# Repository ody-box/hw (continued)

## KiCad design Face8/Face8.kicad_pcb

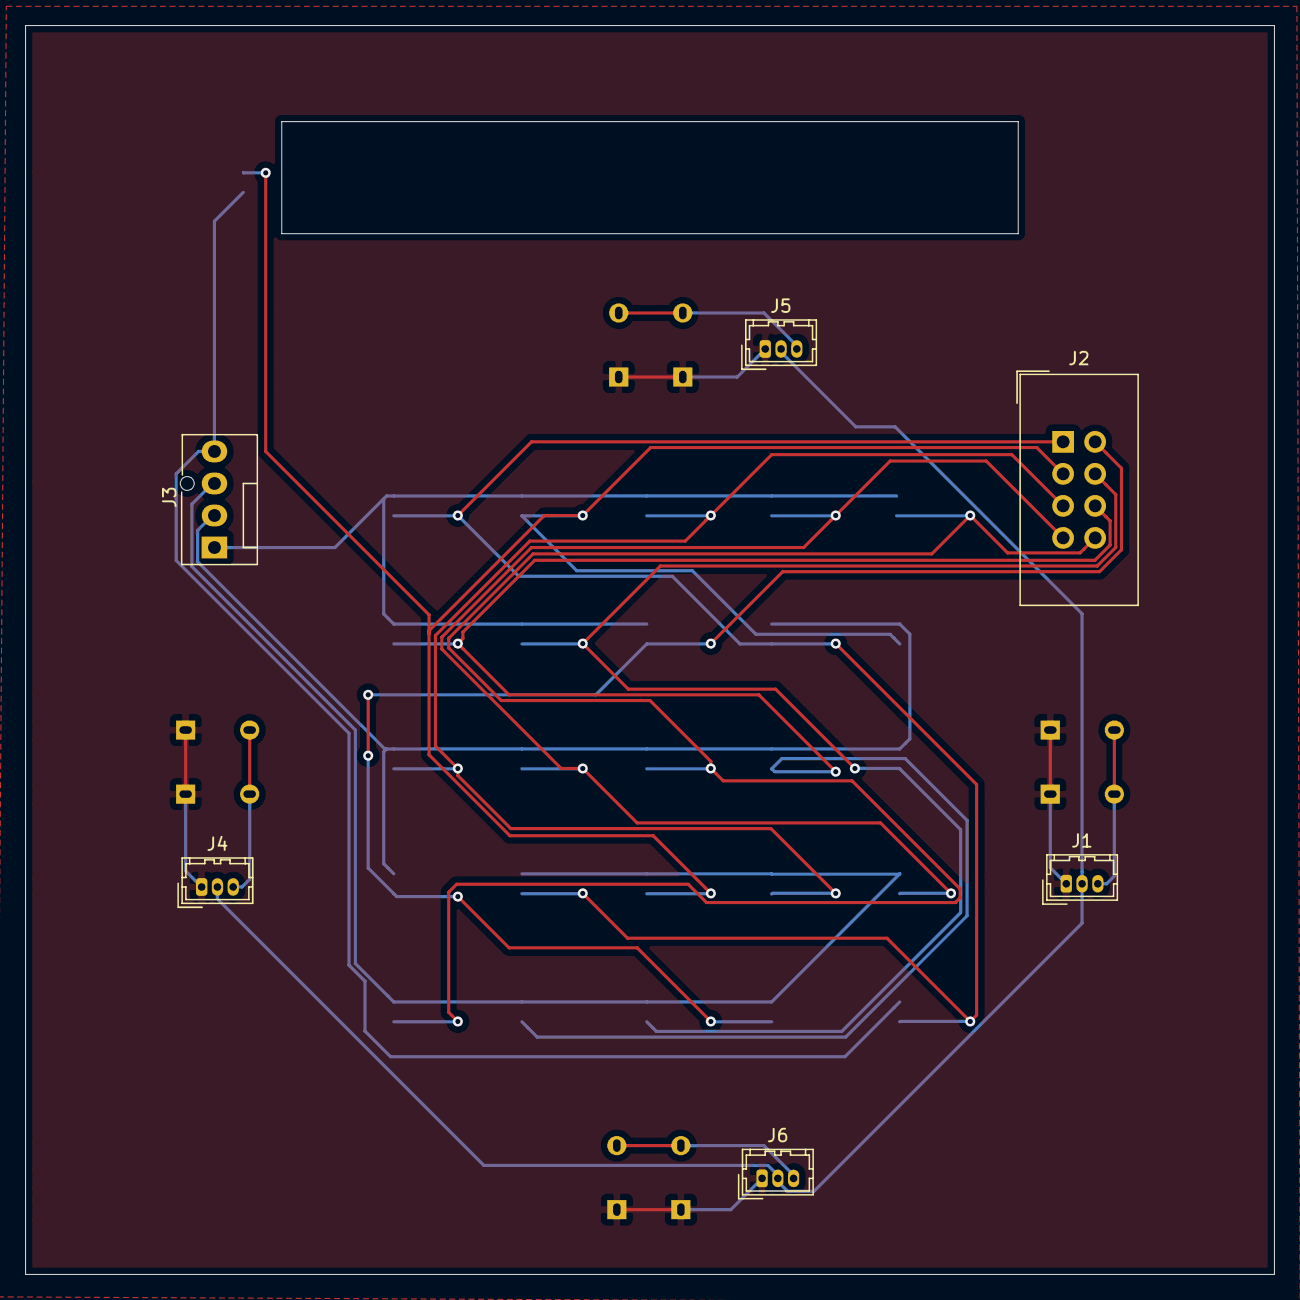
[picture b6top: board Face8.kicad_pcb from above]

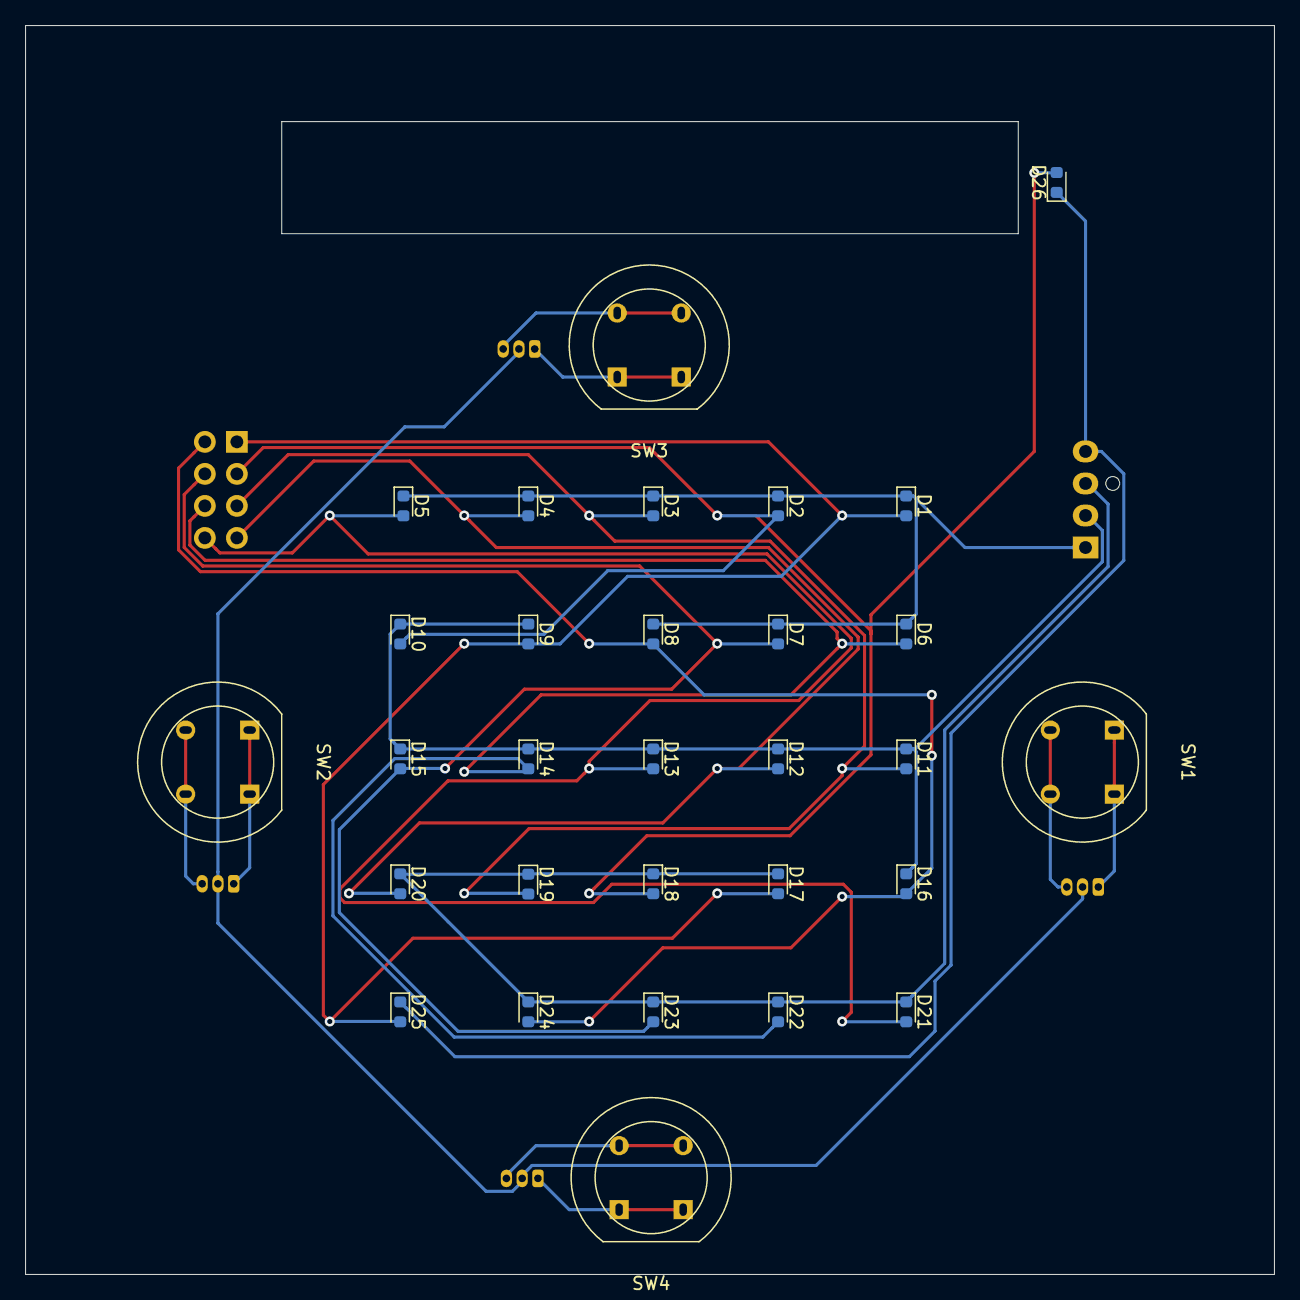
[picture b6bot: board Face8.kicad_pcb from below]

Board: 2 copper layers, 99.1 x 99.1 mm, 36 parts (30 on the bottom side), 18 nets.

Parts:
D1, D2, D3, D4, D5, D6, D7, D8, D9, D10, D11, D12, D13, D14, D15, D16, D17, D18, D19, D20, D21, D22, D23, D24, D25, D26: LED; LED_0603_1608Metric
J1, J4, J5, J6: Conn_01x03_Male; Hirose_DF13-03P-1.25DSA_1x03_P1.25mm_Vertical
J2: Conn_02x04_Odd_Even; IDC-Header_2x04_P2.54mm_Vertical
J3: Conn_01x04_Male; FanPinHeader_1x04_P2.54mm_Vertical
SW1, SW2, SW3, SW4: SW_Push; D6_Switch

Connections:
3.3V: J1.2, J4.2, J5.2, J6.2
DIG0: D1.1, D2.1, D3.1, D4.1, D5.1, D6.1, D7.1, D8.1, J3.1
DIG1: D9.1, D10.1, D11.1, D12.1, D13.1, D14.1, D15.1, D16.1, J3.2
DIG2: D17.1, D18.1, D19.1, D20.1, D21.1, D22.1, D23.1, D24.1, J3.3
DIG3: D25.1, D26.1, J3.4
GND: J1.1, J4.1, J5.1, J6.1, SW1.1, SW2.1, SW3.1, SW4.1
GPIO0: J1.3, SW2.2
GPIO1: J4.3, SW1.2
GPIO2: J5.3, SW3.2
GPIO3: J6.3, SW4.2
SEGA: D1.2, D9.2, D17.2, D25.2, J2.1
SEGB: D2.2, D10.2, D18.2, D26.2, J2.3
SEGC: D3.2, D11.2, D19.2, J2.5
SEGD: D4.2, D12.2, D20.2, J2.7
SEGDP: D8.2, D16.2, D24.2, J2.2
SEGE: D5.2, D13.2, D21.2, J2.8
SEGF: D6.2, D14.2, D22.2, J2.6
SEGG: D7.2, D15.2, D23.2, J2.4

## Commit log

2019-07-02 First commit with Board and Software
2019-07-07 Added Face 248 and 3D
2019-07-14 Changed to multiple AS1105 for LED drivers
2019-07-31 Separated Li-ion charger to face and optimized
2019-09-10 Changed Regulatros to cheaper ones.
